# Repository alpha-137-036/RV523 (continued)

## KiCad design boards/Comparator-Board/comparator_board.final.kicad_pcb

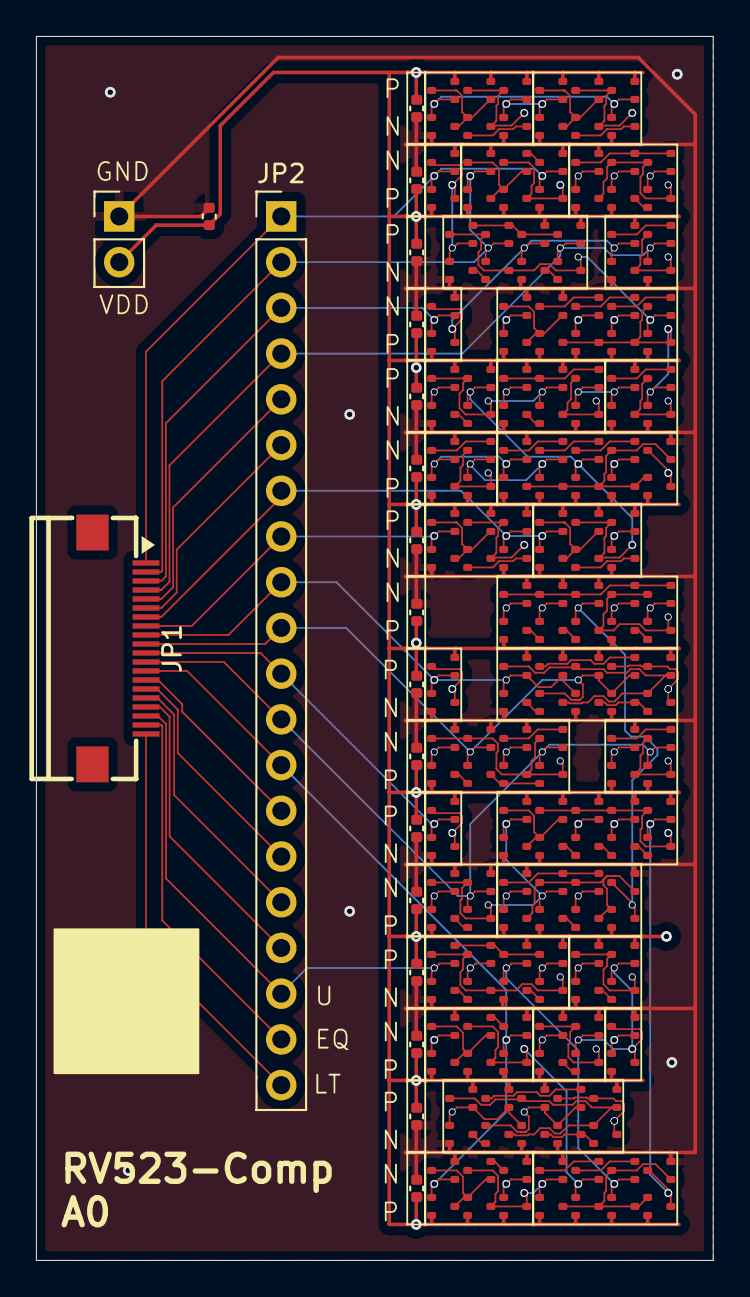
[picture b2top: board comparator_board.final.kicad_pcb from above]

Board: 4 copper layers, 37.6 x 68.0 mm, 216 parts (0 on the bottom side), 118 nets.

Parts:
DECAP1: C_0402_1005Metric
JP1: FFC-SMD_FFC05021-20SBB123W5M
JP2: PinHeader_1x20_P2.54mm_Vertical
JSupply1: PinHeader_1x02_P2.54mm_Vertical
genblk2[0].u_decap.C, genblk2[1].u_decap.C, genblk2[2].u_decap.C, genblk2[3].u_decap.C, genblk2[4].u_decap.C, genblk2[5].u_decap.C, genblk2[6].u_decap.C, genblk2[7].u_decap.C, genblk2[8].u_decap.C, genblk2[9].u_decap.C, genblk2[10].u_decap.C, genblk2[11].u_decap.C, genblk2[12].u_decap.C, genblk2[13].u_decap.C, genblk2[14].u_decap.C, genblk2[15].u_decap.C: 0.1u; C_0402_1005Metric
u_comp._092_.N1, u_comp._093_.N1, u_comp._094_.N1, u_comp._095_.N1, u_comp._096_.N1, u_comp._097_.N1, u_comp._097_.N2, u_comp._097_.N3, u_comp._098_.N1, u_comp._098_.N2, u_comp._098_.N3, u_comp._099_.N1, u_comp._099_.N2, u_comp._100_.N1, u_comp._100_.N2, u_comp._101_.N1, u_comp._101_.N2, u_comp._101_.N3, u_comp._101_.N4, u_comp._101_.N5, u_comp._102_.nand1.N1, u_comp._102_.nand1.N2, u_comp._102_.nand1.N3, u_comp._102_.not1.N1, u_comp._103_.N1, u_comp._103_.N2, u_comp._104_.N1, u_comp._104_.N2, u_comp._105_.N1, u_comp._105_.N2, u_comp._105_.N3, u_comp._105_.N4, u_comp._105_.N5, u_comp._106_.nand4.N1, u_comp._106_.nand4.N2, u_comp._106_.nand4.N3, u_comp._106_.nand4.N4, u_comp._106_.not1.N1, u_comp._107_.N1, u_comp._107_.N2, u_comp._107_.N3, u_comp._108_.N1, u_comp._108_.N2, u_comp._108_.N3, u_comp._109_.N1, u_comp._109_.N2, u_comp._110_.N1, u_comp._110_.N2, u_comp._110_.N3, u_comp._111_.N1, u_comp._111_.N2, u_comp._111_.N3, u_comp._112_.nand1.N1, u_comp._112_.nand1.N2, u_comp._112_.nand1.N3, u_comp._112_.nand1.N4, u_comp._112_.not1.N1, u_comp._113_.N1, u_comp._113_.N2, u_comp._113_.N3, u_comp._113_.N4, u_comp._114_.N1, u_comp._114_.N2, u_comp._115_.N1, u_comp._115_.N2, u_comp._115_.N3, u_comp._116_.nand4.N1, u_comp._116_.nand4.N2, u_comp._116_.nand4.N3, u_comp._116_.nand4.N4, u_comp._116_.not1.N1, u_comp._117_.N1, u_comp._117_.N2, u_comp._118_.N1, u_comp._118_.N2, u_comp._118_.N3, u_comp._119_.N1, u_comp._119_.N2, u_comp._120_.N1, u_comp._120_.N2, u_comp._120_.N3, u_comp._121_.N1, u_comp._121_.N2, u_comp._121_.N3, u_comp._121_.N4, u_comp._122_.N1, u_comp._122_.N2, u_comp._122_.N3, u_comp._122_.N4, u_comp._123_.not1.N1, u_comp._123_.oai.N1, u_comp._123_.oai.N2, u_comp._123_.oai.N3, u_comp._124_.N1, u_comp._124_.N2, u_comp._124_.N3, u_comp._124_.N4, u_comp._124_.N5: NMOS; SOT523
u_comp._092_.P1, u_comp._093_.P1, u_comp._094_.P1, u_comp._095_.P1, u_comp._096_.P1, u_comp._097_.P1, u_comp._097_.P2, u_comp._097_.P3, u_comp._098_.P1, u_comp._098_.P2, u_comp._098_.P3, u_comp._099_.P1, u_comp._099_.P2, u_comp._100_.P1, u_comp._100_.P2, u_comp._101_.P1, u_comp._101_.P2, u_comp._101_.P3, u_comp._101_.P4, u_comp._101_.P5, u_comp._102_.nand1.P1, u_comp._102_.nand1.P2, u_comp._102_.nand1.P3, u_comp._102_.not1.P1, u_comp._103_.P1, u_comp._103_.P2, u_comp._104_.P1, u_comp._104_.P2, u_comp._105_.P1, u_comp._105_.P2, u_comp._105_.P3, u_comp._105_.P4, u_comp._105_.P5, u_comp._106_.nand4.P1, u_comp._106_.nand4.P2, u_comp._106_.nand4.P3, u_comp._106_.nand4.P4, u_comp._106_.not1.P1, u_comp._107_.P1, u_comp._107_.P2, u_comp._107_.P3, u_comp._108_.P1, u_comp._108_.P2, u_comp._108_.P3, u_comp._109_.P1, u_comp._109_.P2, u_comp._110_.P1, u_comp._110_.P2, u_comp._110_.P3, u_comp._111_.P1, u_comp._111_.P2, u_comp._111_.P3, u_comp._112_.nand1.P1, u_comp._112_.nand1.P2, u_comp._112_.nand1.P3, u_comp._112_.nand1.P4, u_comp._112_.not1.P1, u_comp._113_.P1, u_comp._113_.P2, u_comp._113_.P3, u_comp._113_.P4, u_comp._114_.P1, u_comp._114_.P2, u_comp._115_.P1, u_comp._115_.P2, u_comp._115_.P3, u_comp._116_.nand4.P1, u_comp._116_.nand4.P2, u_comp._116_.nand4.P3, u_comp._116_.nand4.P4, u_comp._116_.not1.P1, u_comp._117_.P1, u_comp._117_.P2, u_comp._118_.P1, u_comp._118_.P2, u_comp._118_.P3, u_comp._119_.P1, u_comp._119_.P2, u_comp._120_.P1, u_comp._120_.P2, u_comp._120_.P3, u_comp._121_.P1, u_comp._121_.P2, u_comp._121_.P3, u_comp._121_.P4, u_comp._122_.P1, u_comp._122_.P2, u_comp._122_.P3, u_comp._122_.P4, u_comp._123_.not1.P1, u_comp._123_.oai.P1, u_comp._123_.oai.P2, u_comp._123_.oai.P3, u_comp._124_.P1, u_comp._124_.P2, u_comp._124_.P3, u_comp._124_.P4, u_comp._124_.P5: PMOS; SOT523

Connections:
A.0: JP1.1 (pins.1), JP2.1 (pins.1), u_comp._092_.N1.1 (G), u_comp._092_.P1.1 (G), u_comp._115_.N3.1 (G), u_comp._115_.P3.1 (G)
A.1: JP1.3 (pins.3), JP2.3 (pins.3), u_comp._093_.N1.1 (G), u_comp._093_.P1.1 (G)
A.2: JP1.5 (pins.5), JP2.5 (pins.5), u_comp._108_.N3.1 (G), u_comp._108_.P3.1 (G), u_comp._111_.N1.1 (G), u_comp._111_.P1.1 (G)
A.3: JP1.7 (pins.7), JP2.7 (pins.7), u_comp._107_.N3.1 (G), u_comp._107_.P3.1 (G), u_comp._110_.N1.1 (G), u_comp._110_.P1.1 (G)
A.4: JP1.9 (pins.9), JP2.9 (pins.9), u_comp._094_.N1.1 (G), u_comp._094_.P1.1 (G), u_comp._105_.N1.1 (G), u_comp._105_.N3.1 (G), u_comp._105_.P1.1 (G), u_comp._105_.P3.1 (G)
A.5: JP1.11 (pins.11), JP2.11 (pins.11), u_comp._095_.N1.1 (G), u_comp._095_.P1.1 (G)
A.6: JP1.13 (pins.13), JP2.13 (pins.13), u_comp._097_.N1.1 (G), u_comp._097_.P1.1 (G), u_comp._098_.N3.1 (G), u_comp._098_.P3.1 (G)
A.7: JP1.15 (pins.15), JP2.15 (pins.15), u_comp._099_.N1.1 (G), u_comp._099_.P1.1 (G), u_comp._100_.N1.1 (G), u_comp._100_.P1.1 (G), u_comp._101_.N1.1 (G), u_comp._101_.N3.1 (G), u_comp._101_.P1.1 (G), u_comp._101_.P3.1 (G)
B.0: JP1.2 (pins.2), JP2.2 (pins.2), u_comp._113_.N2.1 (G), u_comp._113_.P2.1 (G), u_comp._115_.N1.1 (G), u_comp._115_.P1.1 (G)
B.1: JP1.4 (pins.4), JP2.4 (pins.4), u_comp._113_.N4.1 (G), u_comp._113_.P4.1 (G), u_comp._114_.N2.1 (G), u_comp._114_.P2.1 (G)
B.2: JP1.6 (pins.6), JP2.6 (pins.6), u_comp._108_.N1.1 (G), u_comp._108_.P1.1 (G), u_comp._111_.N3.1 (G), u_comp._111_.P3.1 (G)
B.3: JP1.8 (pins.8), JP2.8 (pins.8), u_comp._107_.N1.1 (G), u_comp._107_.P1.1 (G), u_comp._110_.N3.1 (G), u_comp._110_.P3.1 (G)
B.4: JP1.10 (pins.10), JP2.10 (pins.10), u_comp._105_.N2.1 (G), u_comp._105_.N4.1 (G), u_comp._105_.P2.1 (G), u_comp._105_.P4.1 (G), u_comp._122_.N2.1 (G), u_comp._122_.P2.1 (G)
B.5: JP1.12 (pins.12), JP2.12 (pins.12), u_comp._103_.N2.1 (G), u_comp._103_.P2.1 (G), u_comp._104_.N2.1 (G), u_comp._104_.P2.1 (G), u_comp._122_.N4.1 (G), u_comp._122_.P4.1 (G)
B.6: JP1.14 (pins.14), JP2.14 (pins.14), u_comp._097_.N3.1 (G), u_comp._097_.P3.1 (G), u_comp._098_.N1.1 (G), u_comp._098_.P1.1 (G)
B.7: JP1.16 (pins.16), JP2.16 (pins.16), u_comp._096_.N1.1 (G), u_comp._096_.P1.1 (G), u_comp._101_.N2.1 (G), u_comp._101_.N4.1 (G), u_comp._101_.P2.1 (G), u_comp._101_.P4.1 (G)
EQ: JP1.19 (pins.19), JP2.19 (pins.19), u_comp._117_.N1.3 (D), u_comp._117_.N2.3 (D), u_comp._117_.P2.3 (D)
GND: DECAP1.2, JSupply1.1 (pins.1), genblk2[0].u_decap.C.1, genblk2[1].u_decap.C.1, genblk2[2].u_decap.C.1, genblk2[3].u_decap.C.1, genblk2[4].u_decap.C.1, genblk2[5].u_decap.C.1, genblk2[6].u_decap.C.1, genblk2[7].u_decap.C.1, genblk2[8].u_decap.C.1, genblk2[9].u_decap.C.1, genblk2[10].u_decap.C.1, genblk2[11].u_decap.C.1, genblk2[12].u_decap.C.1, genblk2[13].u_decap.C.1, genblk2[14].u_decap.C.1, genblk2[15].u_decap.C.1, u_comp._092_.N1.2 (S), u_comp._093_.N1.2 (S), u_comp._094_.N1.2 (S), u_comp._095_.N1.2 (S), u_comp._096_.N1.2 (S), u_comp._097_.N1.2 (S), u_comp._097_.N3.2 (S), u_comp._098_.N1.2 (S), u_comp._098_.N3.2 (S), u_comp._099_.N1.2 (S), u_comp._100_.N1.2 (S), u_comp._100_.N2.2 (S), u_comp._101_.N1.2 (S), u_comp._101_.N3.2 (S), u_comp._101_.N4.2 (S), u_comp._102_.nand1.N1.2 (S), u_comp._102_.not1.N1.2 (S), u_comp._103_.N1.2 (S), u_comp._103_.N2.2 (S), u_comp._104_.N1.2 (S), u_comp._105_.N1.2 (S), u_comp._105_.N3.2 (S), u_comp._105_.N4.2 (S), u_comp._106_.nand4.N1.2 (S), u_comp._106_.not1.N1.2 (S), u_comp._107_.N1.2 (S), u_comp._107_.N3.2 (S), u_comp._108_.N1.2 (S), u_comp._108_.N3.2 (S), u_comp._109_.N1.2 (S), u_comp._110_.N1.2 (S), u_comp._110_.N3.2 (S), u_comp._111_.N1.2 (S), u_comp._111_.N3.2 (S), u_comp._112_.nand1.N1.2 (S), u_comp._112_.not1.N1.2 (S), u_comp._113_.N1.2 (S), u_comp._113_.N3.2 (S), u_comp._114_.N1.2 (S), u_comp._114_.N2.2 (S), u_comp._115_.N1.2 (S), u_comp._115_.N3.2 (S), u_comp._116_.nand4.N1.2 (S), u_comp._116_.not1.N1.2 (S), u_comp._117_.N1.2 (S), u_comp._117_.N2.2 (S), u_comp._118_.N1.2 (S), u_comp._119_.N1.2 (S), u_comp._120_.N1.2 (S), u_comp._120_.N3.2 (S), u_comp._121_.N1.2 (S), u_comp._121_.N3.2 (S), u_comp._122_.N1.2 (S), u_comp._122_.N2.2 (S), u_comp._122_.N3.2 (S), u_comp._123_.not1.N1.2 (S), u_comp._123_.oai.N1.2 (S), u_comp._124_.N1.2 (S), u_comp._124_.N2.2 (S), u_comp._124_.N3.2 (S)
LT: JP1.20 (pins.20), JP2.20 (pins.20), u_comp._124_.N4.3 (D), u_comp._124_.N5.3 (D), u_comp._124_.P3.3 (D), u_comp._124_.P5.3 (D)
U: JP1.18 (pins.18), JP2.18 (pins.18), u_comp._121_.N1.1 (G), u_comp._121_.P1.1 (G), u_comp._124_.N5.1 (G), u_comp._124_.P5.1 (G)
VDD: DECAP1.1, JSupply1.2 (pins.2), genblk2[0].u_decap.C.2, genblk2[1].u_decap.C.2, genblk2[2].u_decap.C.2, genblk2[3].u_decap.C.2, genblk2[4].u_decap.C.2, genblk2[5].u_decap.C.2, genblk2[6].u_decap.C.2, genblk2[7].u_decap.C.2, genblk2[8].u_decap.C.2, genblk2[9].u_decap.C.2, genblk2[10].u_decap.C.2, genblk2[11].u_decap.C.2, genblk2[12].u_decap.C.2, genblk2[13].u_decap.C.2, genblk2[14].u_decap.C.2, genblk2[15].u_decap.C.2, u_comp._092_.P1.2 (S), u_comp._093_.P1.2 (S), u_comp._094_.P1.2 (S), u_comp._095_.P1.2 (S), u_comp._096_.P1.2 (S), u_comp._097_.P1.2 (S), u_comp._097_.P2.2 (S), u_comp._097_.P3.2 (S), u_comp._098_.P1.2 (S), u_comp._098_.P2.2 (S), u_comp._098_.P3.2 (S), u_comp._099_.P1.2 (S), u_comp._099_.P2.2 (S), u_comp._100_.P1.2 (S), u_comp._101_.P1.2 (S), u_comp._101_.P2.2 (S), u_comp._101_.P3.2 (S), u_comp._101_.P5.2 (S), u_comp._102_.nand1.P1.2 (S), u_comp._102_.nand1.P2.2 (S), u_comp._102_.nand1.P3.2 (S), u_comp._102_.not1.P1.2 (S), u_comp._103_.P1.2 (S), u_comp._104_.P1.2 (S), u_comp._104_.P2.2 (S), u_comp._105_.P1.2 (S), u_comp._105_.P2.2 (S), u_comp._105_.P3.2 (S), u_comp._105_.P5.2 (S), u_comp._106_.nand4.P1.2 (S), u_comp._106_.nand4.P2.2 (S), u_comp._106_.nand4.P3.2 (S), u_comp._106_.nand4.P4.2 (S), u_comp._106_.not1.P1.2 (S), u_comp._107_.P1.2 (S), u_comp._107_.P2.2 (S), u_comp._107_.P3.2 (S), u_comp._108_.P1.2 (S), u_comp._108_.P2.2 (S), u_comp._108_.P3.2 (S), u_comp._109_.P1.2 (S), u_comp._109_.P2.2 (S), u_comp._110_.P1.2 (S), u_comp._110_.P2.2 (S), u_comp._110_.P3.2 (S), u_comp._111_.P1.2 (S), u_comp._111_.P2.2 (S), u_comp._111_.P3.2 (S), u_comp._112_.nand1.P1.2 (S), u_comp._112_.nand1.P2.2 (S), u_comp._112_.nand1.P3.2 (S), u_comp._112_.nand1.P4.2 (S), u_comp._112_.not1.P1.2 (S), u_comp._113_.P3.2 (S), u_comp._113_.P4.2 (S), u_comp._114_.P1.2 (S), u_comp._115_.P1.2 (S), u_comp._115_.P2.2 (S), u_comp._115_.P3.2 (S), u_comp._116_.nand4.P1.2 (S), u_comp._116_.nand4.P2.2 (S), u_comp._116_.nand4.P3.2 (S), u_comp._116_.nand4.P4.2 (S), u_comp._116_.not1.P1.2 (S), u_comp._117_.P1.2 (S), u_comp._118_.P1.2 (S), u_comp._118_.P2.2 (S), u_comp._119_.P1.2 (S), u_comp._119_.P2.2 (S), u_comp._120_.P1.2 (S), u_comp._120_.P2.2 (S), u_comp._121_.P3.2 (S), u_comp._121_.P4.2 (S), u_comp._122_.P1.2 (S), u_comp._123_.not1.P1.2 (S), u_comp._123_.oai.P1.2 (S), u_comp._123_.oai.P2.2 (S), u_comp._124_.P1.2 (S), u_comp._124_.P4.2 (S)
pins.17: JP1.17 (pins.17), JP2.17 (pins.17)
u_comp._061_: u_comp._092_.N1.3 (D), u_comp._092_.P1.3 (D), u_comp._113_.N1.1 (G), u_comp._113_.P1.1 (G)
u_comp._062_: u_comp._093_.N1.3 (D), u_comp._093_.P1.3 (D), u_comp._113_.N3.1 (G), u_comp._113_.P3.1 (G), u_comp._114_.N1.1 (G), u_comp._114_.P1.1 (G)
u_comp._063_: u_comp._094_.N1.3 (D), u_comp._094_.P1.3 (D), u_comp._122_.N1.1 (G), u_comp._122_.P1.1 (G)
u_comp._064_: u_comp._095_.N1.3 (D), u_comp._095_.P1.3 (D), u_comp._103_.N1.1 (G), u_comp._103_.P1.1 (G), u_comp._104_.N1.1 (G), u_comp._104_.P1.1 (G), u_comp._122_.N3.1 (G), u_comp._122_.P3.1 (G)
u_comp._065_: u_comp._096_.N1.3 (D), u_comp._096_.P1.3 (D), u_comp._099_.N2.1 (G), u_comp._099_.P2.1 (G), u_comp._100_.N2.1 (G), u_comp._100_.P2.1 (G)
u_comp._066_: u_comp._097_.N2.3 (D), u_comp._097_.P2.3 (D), u_comp._097_.P3.3 (D), u_comp._102_.nand1.N1.1 (G), u_comp._102_.nand1.P1.1 (G)
u_comp._067_: u_comp._098_.N2.3 (D), u_comp._098_.P2.3 (D), u_comp._098_.P3.3 (D), u_comp._102_.nand1.N2.1 (G), u_comp._102_.nand1.P2.1 (G), u_comp._121_.N4.1 (G), u_comp._121_.P4.1 (G)
u_comp._068_: u_comp._099_.N2.3 (D), u_comp._099_.P1.3 (D), u_comp._099_.P2.3 (D), u_comp._124_.N4.1 (G), u_comp._124_.P4.1 (G)
u_comp._069_: u_comp._100_.N1.3 (D), u_comp._100_.N2.3 (D), u_comp._100_.P2.3 (D), u_comp._121_.N2.1 (G), u_comp._121_.P2.1 (G)
u_comp._070_: u_comp._101_.N5.3 (D), u_comp._101_.P4.3 (D), u_comp._101_.P5.3 (D), u_comp._102_.nand1.N3.1 (G), u_comp._102_.nand1.P3.1 (G), u_comp._121_.N3.1 (G), u_comp._121_.P3.1 (G)
u_comp._071_: u_comp._102_.not1.N1.3 (D), u_comp._102_.not1.P1.3 (D), u_comp._106_.nand4.N4.1 (G), u_comp._106_.nand4.P4.1 (G), u_comp._123_.oai.N1.1 (G), u_comp._123_.oai.P1.1 (G)
u_comp._072_: u_comp._103_.N1.3 (D), u_comp._103_.N2.3 (D), u_comp._103_.P2.3 (D), u_comp._106_.not1.N1.1 (G), u_comp._106_.not1.P1.1 (G), u_comp._123_.oai.N2.1 (G), u_comp._123_.oai.P2.1 (G)
u_comp._073_: u_comp._104_.N2.3 (D), u_comp._104_.P1.3 (D), u_comp._104_.P2.3 (D), u_comp._106_.nand4.N2.1 (G), u_comp._106_.nand4.P2.1 (G)
u_comp._074_: u_comp._105_.N5.3 (D), u_comp._105_.P4.3 (D), u_comp._105_.P5.3 (D), u_comp._106_.nand4.N3.1 (G), u_comp._106_.nand4.P3.1 (G)
u_comp._075_: u_comp._106_.nand4.N4.3 (D), u_comp._106_.nand4.P1.3 (D), u_comp._106_.nand4.P2.3 (D), u_comp._106_.nand4.P3.3 (D), u_comp._106_.nand4.P4.3 (D), u_comp._117_.N1.1 (G), u_comp._117_.P1.1 (G), u_comp._120_.N3.1 (G), u_comp._120_.P3.1 (G)
u_comp._076_: u_comp._107_.N2.3 (D), u_comp._107_.P2.3 (D), u_comp._107_.P3.3 (D), u_comp._109_.N1.1 (G), u_comp._109_.P1.1 (G), u_comp._112_.nand1.N1.1 (G), u_comp._112_.nand1.P1.1 (G)
u_comp._077_: u_comp._108_.N2.3 (D), u_comp._108_.P2.3 (D), u_comp._108_.P3.3 (D), u_comp._109_.N2.1 (G), u_comp._109_.P2.1 (G), u_comp._112_.nand1.N2.1 (G), u_comp._112_.nand1.P2.1 (G)
u_comp._078_: u_comp._109_.N2.3 (D), u_comp._109_.P1.3 (D), u_comp._109_.P2.3 (D), u_comp._119_.N1.1 (G), u_comp._119_.P1.1 (G)
u_comp._079_: u_comp._110_.N2.3 (D), u_comp._110_.P2.3 (D), u_comp._110_.P3.3 (D), u_comp._112_.nand1.N3.1 (G), u_comp._112_.nand1.P3.1 (G), u_comp._119_.N2.1 (G), u_comp._119_.P2.1 (G)
u_comp._080_: u_comp._111_.N2.3 (D), u_comp._111_.P2.3 (D), u_comp._111_.P3.3 (D), u_comp._112_.nand1.N4.1 (G), u_comp._112_.nand1.P4.1 (G)
u_comp._081_: u_comp._112_.not1.N1.3 (D), u_comp._112_.not1.P1.3 (D), u_comp._116_.nand4.N3.1 (G), u_comp._116_.nand4.P3.1 (G), u_comp._118_.N1.1 (G), u_comp._118_.P1.1 (G)
u_comp._082_: u_comp._113_.N2.3 (D), u_comp._113_.N4.3 (D), u_comp._113_.P1.3 (D), u_comp._113_.P2.3 (D), u_comp._116_.nand4.N4.1 (G), u_comp._116_.nand4.P4.1 (G), u_comp._118_.N2.1 (G), u_comp._118_.P2.1 (G)
u_comp._083_: u_comp._114_.N1.3 (D), u_comp._114_.N2.3 (D), u_comp._114_.P2.3 (D), u_comp._116_.not1.N1.1 (G), u_comp._116_.not1.P1.1 (G), u_comp._118_.N3.1 (G), u_comp._118_.P3.1 (G)
u_comp._084_: u_comp._115_.N2.3 (D), u_comp._115_.P2.3 (D), u_comp._115_.P3.3 (D), u_comp._116_.nand4.N2.1 (G), u_comp._116_.nand4.P2.1 (G)
u_comp._085_: u_comp._116_.nand4.N4.3 (D), u_comp._116_.nand4.P1.3 (D), u_comp._116_.nand4.P2.3 (D), u_comp._116_.nand4.P3.3 (D), u_comp._116_.nand4.P4.3 (D), u_comp._117_.N2.1 (G), u_comp._117_.P2.1 (G)
u_comp._086_: u_comp._118_.N2.3 (D), u_comp._118_.N3.3 (D), u_comp._118_.P1.3 (D), u_comp._118_.P3.3 (D), u_comp._120_.N1.1 (G), u_comp._120_.P1.1 (G)
u_comp._087_: u_comp._119_.N2.3 (D), u_comp._119_.P1.3 (D), u_comp._119_.P2.3 (D), u_comp._120_.N2.1 (G), u_comp._120_.P2.1 (G)
u_comp._088_: u_comp._120_.N2.3 (D), u_comp._120_.N3.3 (D), u_comp._120_.P3.3 (D), u_comp._124_.N1.1 (G), u_comp._124_.P1.1 (G)
u_comp._089_: u_comp._121_.N2.3 (D), u_comp._121_.N4.3 (D), u_comp._121_.P1.3 (D), u_comp._121_.P2.3 (D), u_comp._124_.N2.1 (G), u_comp._124_.P2.1 (G)
u_comp._090_: u_comp._122_.N1.3 (D), u_comp._122_.N2.3 (D), u_comp._122_.N4.3 (D), u_comp._122_.P3.3 (D), u_comp._122_.P4.3 (D), u_comp._123_.oai.N3.1 (G), u_comp._123_.oai.P3.1 (G)
u_comp._091_: u_comp._123_.not1.N1.3 (D), u_comp._123_.not1.P1.3 (D), u_comp._124_.N3.1 (G), u_comp._124_.P3.1 (G)
u_comp._097_.A: u_comp._097_.N1.3 (D), u_comp._097_.N2.1 (G), u_comp._097_.P1.3 (D), u_comp._097_.P2.1 (G)
u_comp._097_.sndA: u_comp._097_.N2.2 (S), u_comp._097_.N3.3 (D)
u_comp._098_.A: u_comp._098_.N1.3 (D), u_comp._098_.N2.1 (G), u_comp._098_.P1.3 (D), u_comp._098_.P2.1 (G)
u_comp._098_.sndA: u_comp._098_.N2.2 (S), u_comp._098_.N3.3 (D)
u_comp._099_.int1: u_comp._099_.N1.3 (D), u_comp._099_.N2.2 (S)
u_comp._100_.C: u_comp._100_.P1.3 (D), u_comp._100_.P2.2 (S)
u_comp._101_.inand: u_comp._101_.N2.3 (D), u_comp._101_.N5.1 (G), u_comp._101_.P1.3 (D), u_comp._101_.P2.3 (D), u_comp._101_.P5.1 (G)
u_comp._101_.nmid: u_comp._101_.N3.3 (D), u_comp._101_.N4.3 (D), u_comp._101_.N5.2 (S)
u_comp._101_.sndNA: u_comp._101_.N1.3 (D), u_comp._101_.N2.2 (S)
u_comp._101_.sndPA: u_comp._101_.P3.3 (D), u_comp._101_.P4.2 (S)
u_comp._102_.nY: u_comp._102_.nand1.N3.3 (D), u_comp._102_.nand1.P1.3 (D), u_comp._102_.nand1.P2.3 (D), u_comp._102_.nand1.P3.3 (D), u_comp._102_.not1.N1.1 (G), u_comp._102_.not1.P1.1 (G)
u_comp._102_.nand1.int1: u_comp._102_.nand1.N1.3 (D), u_comp._102_.nand1.N2.2 (S)
u_comp._102_.nand1.int2: u_comp._102_.nand1.N2.3 (D), u_comp._102_.nand1.N3.2 (S)
u_comp._103_.C: u_comp._103_.P1.3 (D), u_comp._103_.P2.2 (S)
u_comp._104_.int1: u_comp._104_.N1.3 (D), u_comp._104_.N2.2 (S)
u_comp._105_.inand: u_comp._105_.N2.3 (D), u_comp._105_.N5.1 (G), u_comp._105_.P1.3 (D), u_comp._105_.P2.3 (D), u_comp._105_.P5.1 (G)
u_comp._105_.nmid: u_comp._105_.N3.3 (D), u_comp._105_.N4.3 (D), u_comp._105_.N5.2 (S)
u_comp._105_.sndNA: u_comp._105_.N1.3 (D), u_comp._105_.N2.2 (S)
u_comp._105_.sndPA: u_comp._105_.P3.3 (D), u_comp._105_.P4.2 (S)
u_comp._106_.A1: u_comp._106_.nand4.N1.1 (G), u_comp._106_.nand4.P1.1 (G), u_comp._106_.not1.N1.3 (D), u_comp._106_.not1.P1.3 (D)
u_comp._106_.nand4.int1: u_comp._106_.nand4.N1.3 (D), u_comp._106_.nand4.N2.2 (S)
u_comp._106_.nand4.int2: u_comp._106_.nand4.N2.3 (D), u_comp._106_.nand4.N3.2 (S)
u_comp._106_.nand4.int3: u_comp._106_.nand4.N3.3 (D), u_comp._106_.nand4.N4.2 (S)
u_comp._107_.A: u_comp._107_.N1.3 (D), u_comp._107_.N2.1 (G), u_comp._107_.P1.3 (D), u_comp._107_.P2.1 (G)
u_comp._107_.sndA: u_comp._107_.N2.2 (S), u_comp._107_.N3.3 (D)
u_comp._108_.A: u_comp._108_.N1.3 (D), u_comp._108_.N2.1 (G), u_comp._108_.P1.3 (D), u_comp._108_.P2.1 (G)
u_comp._108_.sndA: u_comp._108_.N2.2 (S), u_comp._108_.N3.3 (D)
u_comp._109_.int1: u_comp._109_.N1.3 (D), u_comp._109_.N2.2 (S)
u_comp._110_.A: u_comp._110_.N1.3 (D), u_comp._110_.N2.1 (G), u_comp._110_.P1.3 (D), u_comp._110_.P2.1 (G)
u_comp._110_.sndA: u_comp._110_.N2.2 (S), u_comp._110_.N3.3 (D)
u_comp._111_.A: u_comp._111_.N1.3 (D), u_comp._111_.N2.1 (G), u_comp._111_.P1.3 (D), u_comp._111_.P2.1 (G)
u_comp._111_.sndA: u_comp._111_.N2.2 (S), u_comp._111_.N3.3 (D)
u_comp._112_.nY: u_comp._112_.nand1.N4.3 (D), u_comp._112_.nand1.P1.3 (D), u_comp._112_.nand1.P2.3 (D), u_comp._112_.nand1.P3.3 (D), u_comp._112_.nand1.P4.3 (D), u_comp._112_.not1.N1.1 (G), u_comp._112_.not1.P1.1 (G)
u_comp._112_.nand1.int1: u_comp._112_.nand1.N1.3 (D), u_comp._112_.nand1.N2.2 (S)
u_comp._112_.nand1.int2: u_comp._112_.nand1.N2.3 (D), u_comp._112_.nand1.N3.2 (S)
u_comp._112_.nand1.int3: u_comp._112_.nand1.N3.3 (D), u_comp._112_.nand1.N4.2 (S)
u_comp._113_.intA: u_comp._113_.N1.3 (D), u_comp._113_.N2.2 (S)
u_comp._113_.intB: u_comp._113_.N3.3 (D), u_comp._113_.N4.2 (S)
u_comp._113_.intP: u_comp._113_.P1.2 (S), u_comp._113_.P2.2 (S), u_comp._113_.P3.3 (D), u_comp._113_.P4.3 (D)
u_comp._114_.C: u_comp._114_.P1.3 (D), u_comp._114_.P2.2 (S)
u_comp._115_.A: u_comp._115_.N1.3 (D), u_comp._115_.N2.1 (G), u_comp._115_.P1.3 (D), u_comp._115_.P2.1 (G)
u_comp._115_.sndA: u_comp._115_.N2.2 (S), u_comp._115_.N3.3 (D)
u_comp._116_.A1: u_comp._116_.nand4.N1.1 (G), u_comp._116_.nand4.P1.1 (G), u_comp._116_.not1.N1.3 (D), u_comp._116_.not1.P1.3 (D)
u_comp._116_.nand4.int1: u_comp._116_.nand4.N1.3 (D), u_comp._116_.nand4.N2.2 (S)
u_comp._116_.nand4.int2: u_comp._116_.nand4.N2.3 (D), u_comp._116_.nand4.N3.2 (S)
u_comp._116_.nand4.int3: u_comp._116_.nand4.N3.3 (D), u_comp._116_.nand4.N4.2 (S)
u_comp._117_.C: u_comp._117_.P1.3 (D), u_comp._117_.P2.2 (S)
u_comp._118_.intB: u_comp._118_.P2.3 (D), u_comp._118_.P3.2 (S)
u_comp._118_.intN: u_comp._118_.N1.3 (D), u_comp._118_.N2.2 (S), u_comp._118_.N3.2 (S)
u_comp._119_.int1: u_comp._119_.N1.3 (D), u_comp._119_.N2.2 (S)
u_comp._120_.pndA: u_comp._120_.P1.3 (D), u_comp._120_.P2.3 (D), u_comp._120_.P3.2 (S)
u_comp._120_.sndA1: u_comp._120_.N1.3 (D), u_comp._120_.N2.2 (S)
u_comp._121_.intA: u_comp._121_.N1.3 (D), u_comp._121_.N2.2 (S)
u_comp._121_.intB: u_comp._121_.N3.3 (D), u_comp._121_.N4.2 (S)
u_comp._121_.intP: u_comp._121_.P1.2 (S), u_comp._121_.P2.2 (S), u_comp._121_.P3.3 (D), u_comp._121_.P4.3 (D)
u_comp._122_.intC: u_comp._122_.N3.3 (D), u_comp._122_.N4.2 (S)
u_comp._122_.intPA: u_comp._122_.P1.3 (D), u_comp._122_.P2.2 (S)
u_comp._122_.intPB: u_comp._122_.P2.3 (D), u_comp._122_.P3.2 (S), u_comp._122_.P4.2 (S)
u_comp._123_.Y_N: u_comp._123_.not1.N1.1 (G), u_comp._123_.not1.P1.1 (G), u_comp._123_.oai.N2.3 (D), u_comp._123_.oai.N3.3 (D), u_comp._123_.oai.P1.3 (D), u_comp._123_.oai.P3.3 (D)
u_comp._123_.oai.intB: u_comp._123_.oai.P2.3 (D), u_comp._123_.oai.P3.2 (S)
u_comp._123_.oai.intN: u_comp._123_.oai.N1.3 (D), u_comp._123_.oai.N2.2 (S), u_comp._123_.oai.N3.2 (S)
u_comp._124_.intN: u_comp._124_.N1.3 (D), u_comp._124_.N2.3 (D), u_comp._124_.N3.3 (D), u_comp._124_.N4.2 (S), u_comp._124_.N5.2 (S)
u_comp._124_.intPA1: u_comp._124_.P1.3 (D), u_comp._124_.P2.2 (S)
u_comp._124_.intPA2: u_comp._124_.P2.3 (D), u_comp._124_.P3.2 (S)
u_comp._124_.intPB1: u_comp._124_.P4.3 (D), u_comp._124_.P5.2 (S)

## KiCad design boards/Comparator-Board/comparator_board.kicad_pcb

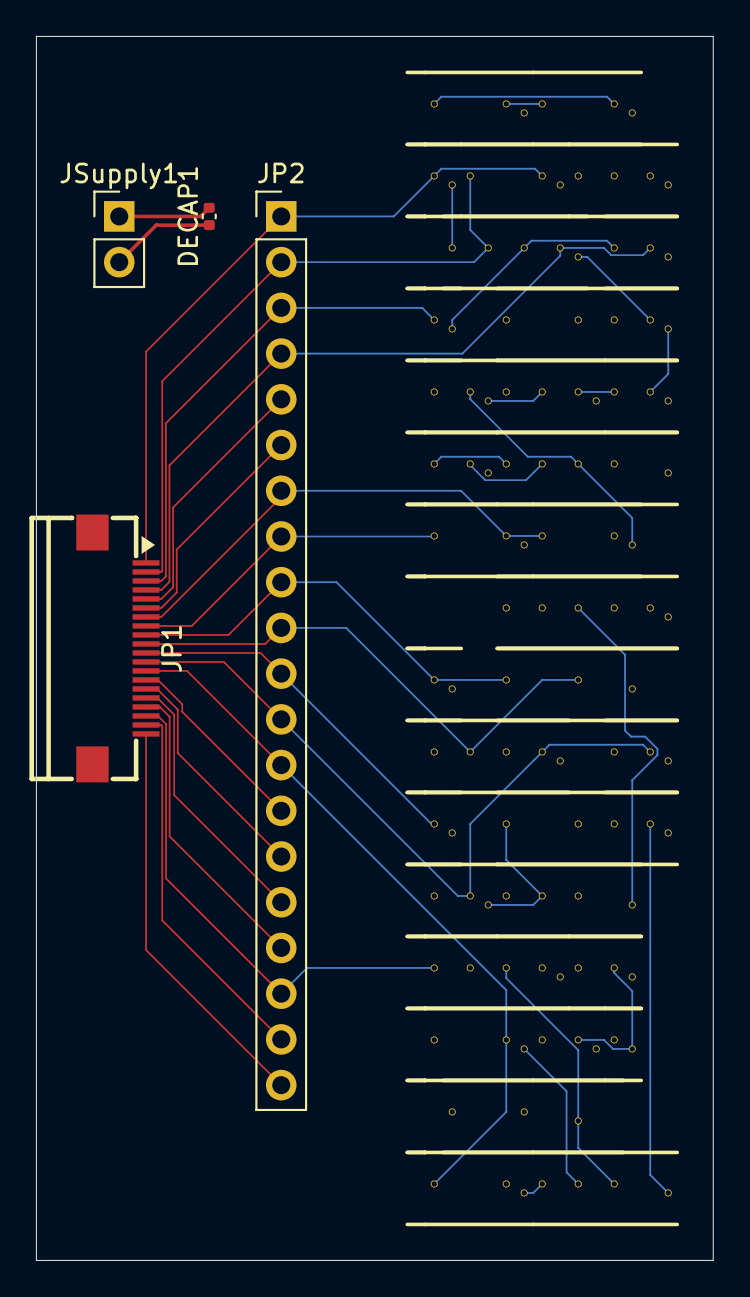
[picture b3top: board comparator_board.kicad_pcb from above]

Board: 4 copper layers, 37.6 x 68.0 mm, 53 parts (0 on the bottom side), 53 nets.

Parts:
DECAP1: C_0402_1005Metric
JP1: FFC-SMD_FFC05021-20SBB123W5M
JP2: PinHeader_1x20_P2.54mm_Vertical
JSupply1: PinHeader_1x02_P2.54mm_Vertical
genblk2[0].u_decap, genblk2[1].u_decap, genblk2[2].u_decap, genblk2[3].u_decap, genblk2[4].u_decap, genblk2[5].u_decap, genblk2[6].u_decap, genblk2[7].u_decap, genblk2[8].u_decap, genblk2[9].u_decap, genblk2[10].u_decap, genblk2[11].u_decap, genblk2[12].u_decap, genblk2[13].u_decap, genblk2[14].u_decap, genblk2[15].u_decap: DECAP
u_comp._092_, u_comp._093_, u_comp._094_, u_comp._095_, u_comp._096_: NOT
u_comp._097_, u_comp._098_, u_comp._107_, u_comp._108_, u_comp._110_, u_comp._111_, u_comp._115_: NAND2B
u_comp._099_, u_comp._104_, u_comp._109_, u_comp._119_: NAND2
u_comp._100_, u_comp._103_, u_comp._114_, u_comp._117_: NOR2
u_comp._101_, u_comp._105_: XNOR2
u_comp._102_: AND3
u_comp._106_, u_comp._116_: NAND4B
u_comp._112_: AND4
u_comp._113_, u_comp._121_: AOI22
u_comp._118_: OAI21
u_comp._120_: AOI21
u_comp._122_: AOI211
u_comp._123_: OA21
u_comp._124_: OAI32

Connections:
A.0: JP1.1 (pins.1), JP2.1 (pins.1), u_comp._092_.A, u_comp._115_.B
A.1: JP1.3 (pins.3), JP2.3 (pins.3), u_comp._093_.A
A.2: JP1.5 (pins.5), JP2.5 (pins.5), u_comp._108_.B, u_comp._111_.A_N
A.3: JP1.7 (pins.7), JP2.7 (pins.7), u_comp._107_.B, u_comp._110_.A_N
A.4: JP1.9 (pins.9), JP2.9 (pins.9), u_comp._094_.A, u_comp._105_.A
A.5: JP1.11 (pins.11), JP2.11 (pins.11), u_comp._095_.A
A.6: JP1.13 (pins.13), JP2.13 (pins.13), u_comp._097_.A_N, u_comp._098_.B
A.7: JP1.15 (pins.15), JP2.15 (pins.15), u_comp._099_.A1, u_comp._100_.A1, u_comp._101_.A
B.0: JP1.2 (pins.2), JP2.2 (pins.2), u_comp._113_.A2, u_comp._115_.A_N
B.1: JP1.4 (pins.4), JP2.4 (pins.4), u_comp._113_.B2, u_comp._114_.A2
B.2: JP1.6 (pins.6), JP2.6 (pins.6), u_comp._108_.A_N, u_comp._111_.B
B.3: JP1.8 (pins.8), JP2.8 (pins.8), u_comp._107_.A_N, u_comp._110_.B
B.4: JP1.10 (pins.10), JP2.10 (pins.10), u_comp._105_.B, u_comp._122_.B
B.5: JP1.12 (pins.12), JP2.12 (pins.12), u_comp._103_.A2, u_comp._104_.A2, u_comp._122_.C2
B.6: JP1.14 (pins.14), JP2.14 (pins.14), u_comp._097_.B, u_comp._098_.A_N
B.7: JP1.16 (pins.16), JP2.16 (pins.16), u_comp._096_.A, u_comp._101_.B
EQ: JP1.19 (pins.19), JP2.19 (pins.19), u_comp._117_.Y
GND: DECAP1.2, JSupply1.1 (pins.1)
LT: JP1.20 (pins.20), JP2.20 (pins.20), u_comp._124_.Y
U: JP1.18 (pins.18), JP2.18 (pins.18), u_comp._121_.A1, u_comp._124_.B2
VDD: DECAP1.1, JSupply1.2 (pins.2)
pins.17: JP1.17 (pins.17), JP2.17 (pins.17)
u_comp._061_: u_comp._092_.Y, u_comp._113_.A1
u_comp._062_: u_comp._093_.Y, u_comp._113_.B1, u_comp._114_.A1
u_comp._063_: u_comp._094_.Y, u_comp._122_.A
u_comp._064_: u_comp._095_.Y, u_comp._103_.A1, u_comp._104_.A1, u_comp._122_.C1
u_comp._065_: u_comp._096_.Y, u_comp._099_.A2, u_comp._100_.A2
u_comp._066_: u_comp._097_.Y, u_comp._102_.A1
u_comp._067_: u_comp._098_.Y, u_comp._102_.A2, u_comp._121_.B2
u_comp._068_: u_comp._099_.Y, u_comp._124_.B1
u_comp._069_: u_comp._100_.Y, u_comp._121_.A2
u_comp._070_: u_comp._101_.Y, u_comp._102_.A3, u_comp._121_.B1
u_comp._071_: u_comp._102_.Y, u_comp._106_.A4, u_comp._123_.A
u_comp._072_: u_comp._103_.Y, u_comp._106_.A1_N, u_comp._123_.B1
u_comp._073_: u_comp._104_.Y, u_comp._106_.A2
u_comp._074_: u_comp._105_.Y, u_comp._106_.A3
u_comp._075_: u_comp._106_.Y, u_comp._117_.A1, u_comp._120_.B1
u_comp._076_: u_comp._107_.Y, u_comp._109_.A1, u_comp._112_.A1
u_comp._077_: u_comp._108_.Y, u_comp._109_.A2, u_comp._112_.A2
u_comp._078_: u_comp._109_.Y, u_comp._119_.A1
u_comp._079_: u_comp._110_.Y, u_comp._112_.A3, u_comp._119_.A2
u_comp._080_: u_comp._111_.Y, u_comp._112_.A4
u_comp._081_: u_comp._112_.Y, u_comp._116_.A3, u_comp._118_.A
u_comp._082_: u_comp._113_.Y, u_comp._116_.A4, u_comp._118_.B1
u_comp._083_: u_comp._114_.Y, u_comp._116_.A1_N, u_comp._118_.B2
u_comp._084_: u_comp._115_.Y, u_comp._116_.A2
u_comp._085_: u_comp._116_.Y, u_comp._117_.A2
u_comp._086_: u_comp._118_.Y, u_comp._120_.A1
u_comp._087_: u_comp._119_.Y, u_comp._120_.A2
u_comp._088_: u_comp._120_.Y, u_comp._124_.A1
u_comp._089_: u_comp._121_.Y, u_comp._124_.A2
u_comp._090_: u_comp._122_.Y, u_comp._123_.B2
u_comp._091_: u_comp._123_.Y, u_comp._124_.A3

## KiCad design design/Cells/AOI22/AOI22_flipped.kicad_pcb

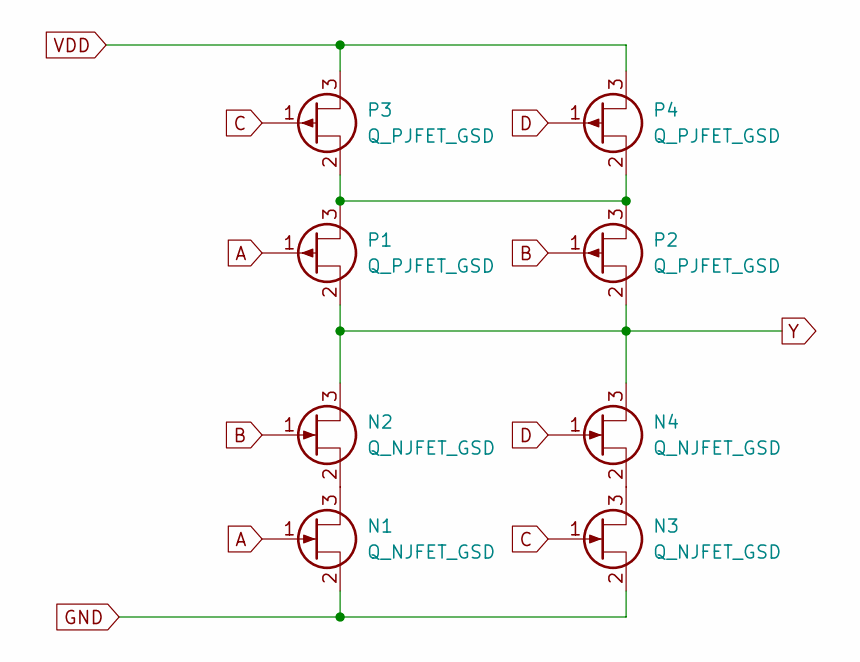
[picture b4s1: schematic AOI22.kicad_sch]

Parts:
N1, N2, N3, N4: Q_NJFET_GSD; SOT-523
P1, P2, P3, P4: Q_PJFET_GSD; SOT-523

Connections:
A: N1.1 (G), P1.1 (G)
B: N2.1 (G), P2.1 (G)
C: N3.1 (G), P3.1 (G)
D: N4.1 (G), P4.1 (G)
GND: N1.2 (S), N3.2 (S)
unnamed: N1.3 (D), N2.2 (S)
unnamed: N3.3 (D), N4.2 (S)
unnamed: P1.3 (D), P2.3 (D), P3.2 (S), P4.2 (S)
VDD: P3.3 (D), P4.3 (D)
Y: N2.3 (D), N4.3 (D), P1.2 (S), P2.2 (S)

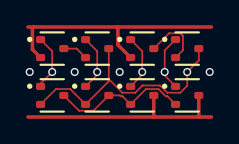
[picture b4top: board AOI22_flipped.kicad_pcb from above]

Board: 2 copper layers, 8 parts (0 on the bottom side), 10 nets.

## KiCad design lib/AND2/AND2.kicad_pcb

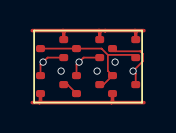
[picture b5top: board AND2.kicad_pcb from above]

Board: 2 copper layers, 6 parts (0 on the bottom side), 7 nets.

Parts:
nand1.N1, nand1.N2: NMOS; SOT523
nand1.P1, nand1.P2: PMOS; SOT523
not1.N1: NMOS; SOT523
not1.P1: PMOS; SOT523

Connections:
A1: nand1.N1.1 (G), nand1.P1.1 (G)
A2: nand1.N2.1 (G), nand1.P2.1 (G)
GND: nand1.N1.2 (S), not1.N1.2 (S)
VDD: nand1.P1.2 (S), nand1.P2.2 (S), not1.P1.2 (S)
Y: not1.N1.3 (D), not1.P1.3 (D)
nY: nand1.N2.3 (D), nand1.P1.3 (D), nand1.P2.3 (D), not1.N1.1 (G), not1.P1.1 (G)
nand1.int1: nand1.N1.3 (D), nand1.N2.2 (S)
